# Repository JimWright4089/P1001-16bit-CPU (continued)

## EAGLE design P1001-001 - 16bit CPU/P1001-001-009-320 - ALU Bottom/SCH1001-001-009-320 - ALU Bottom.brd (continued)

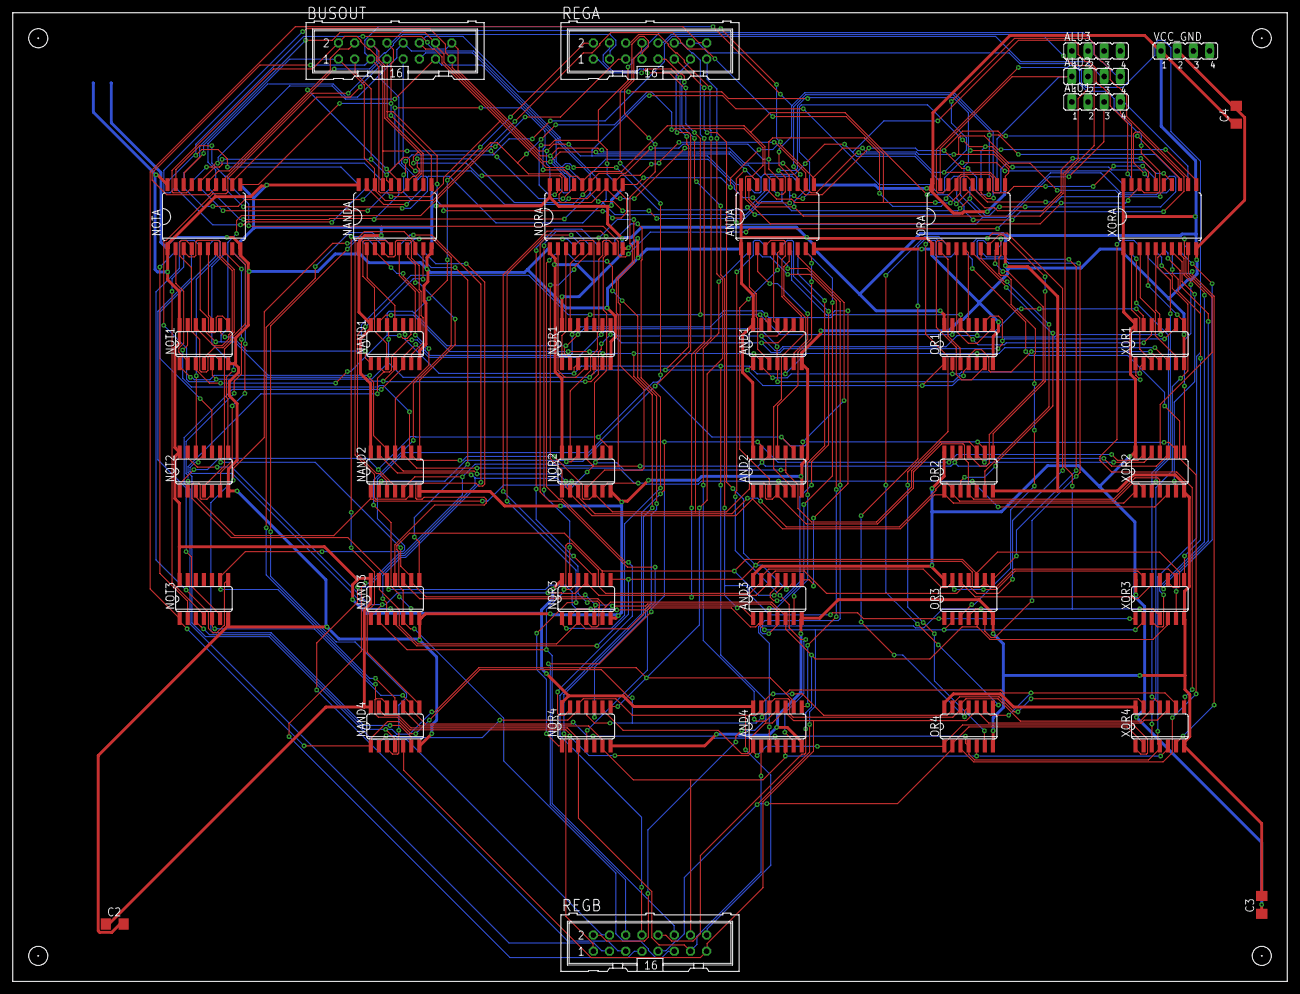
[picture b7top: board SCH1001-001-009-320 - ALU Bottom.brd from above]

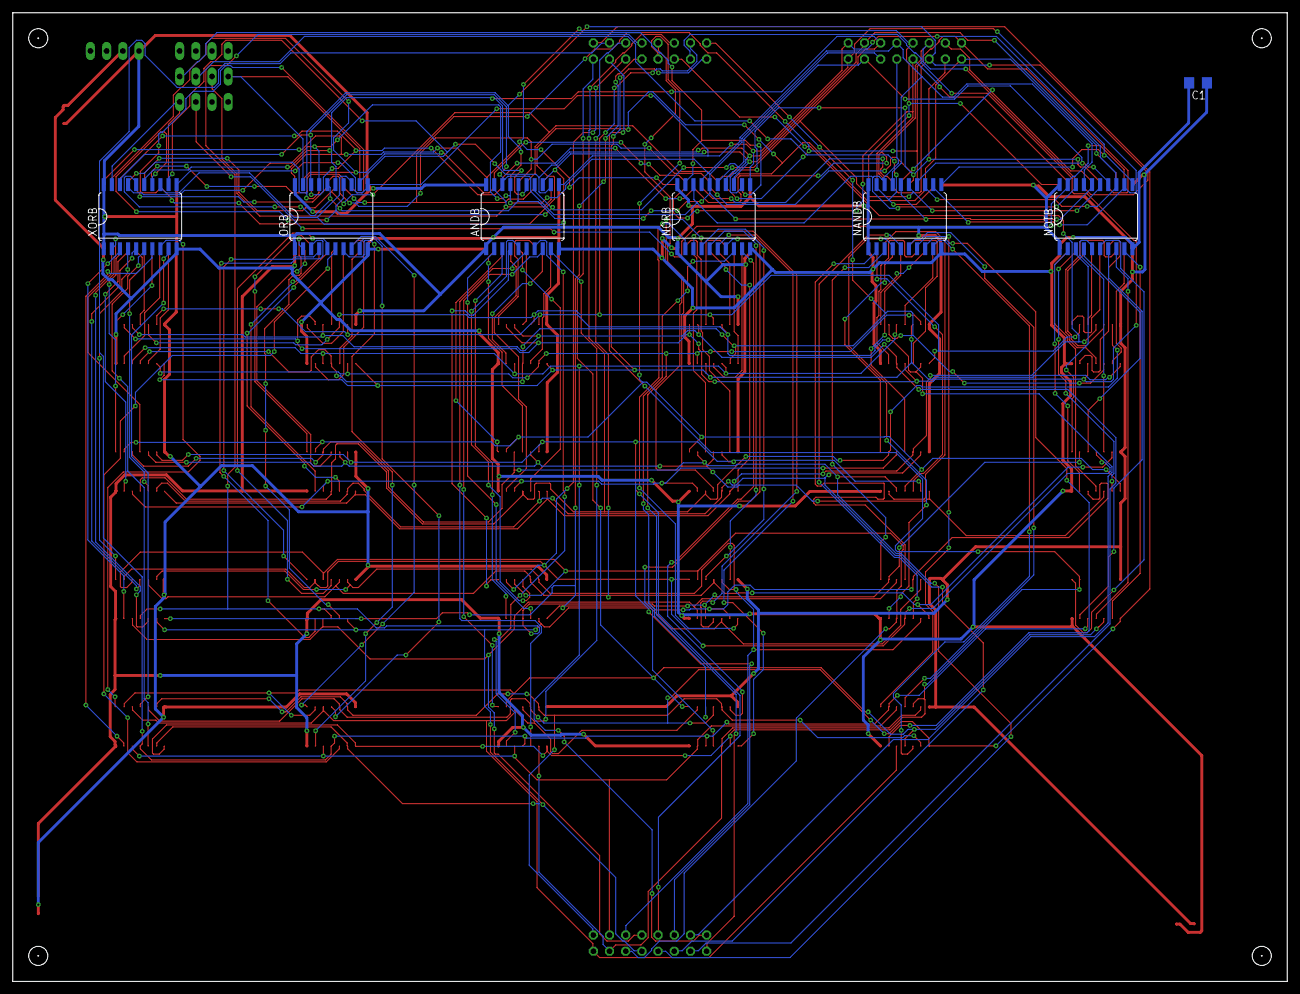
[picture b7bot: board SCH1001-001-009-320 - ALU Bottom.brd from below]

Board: 2 copper layers, 200.0 x 152.0 mm, 46 parts (7 on the bottom side), 152 nets.

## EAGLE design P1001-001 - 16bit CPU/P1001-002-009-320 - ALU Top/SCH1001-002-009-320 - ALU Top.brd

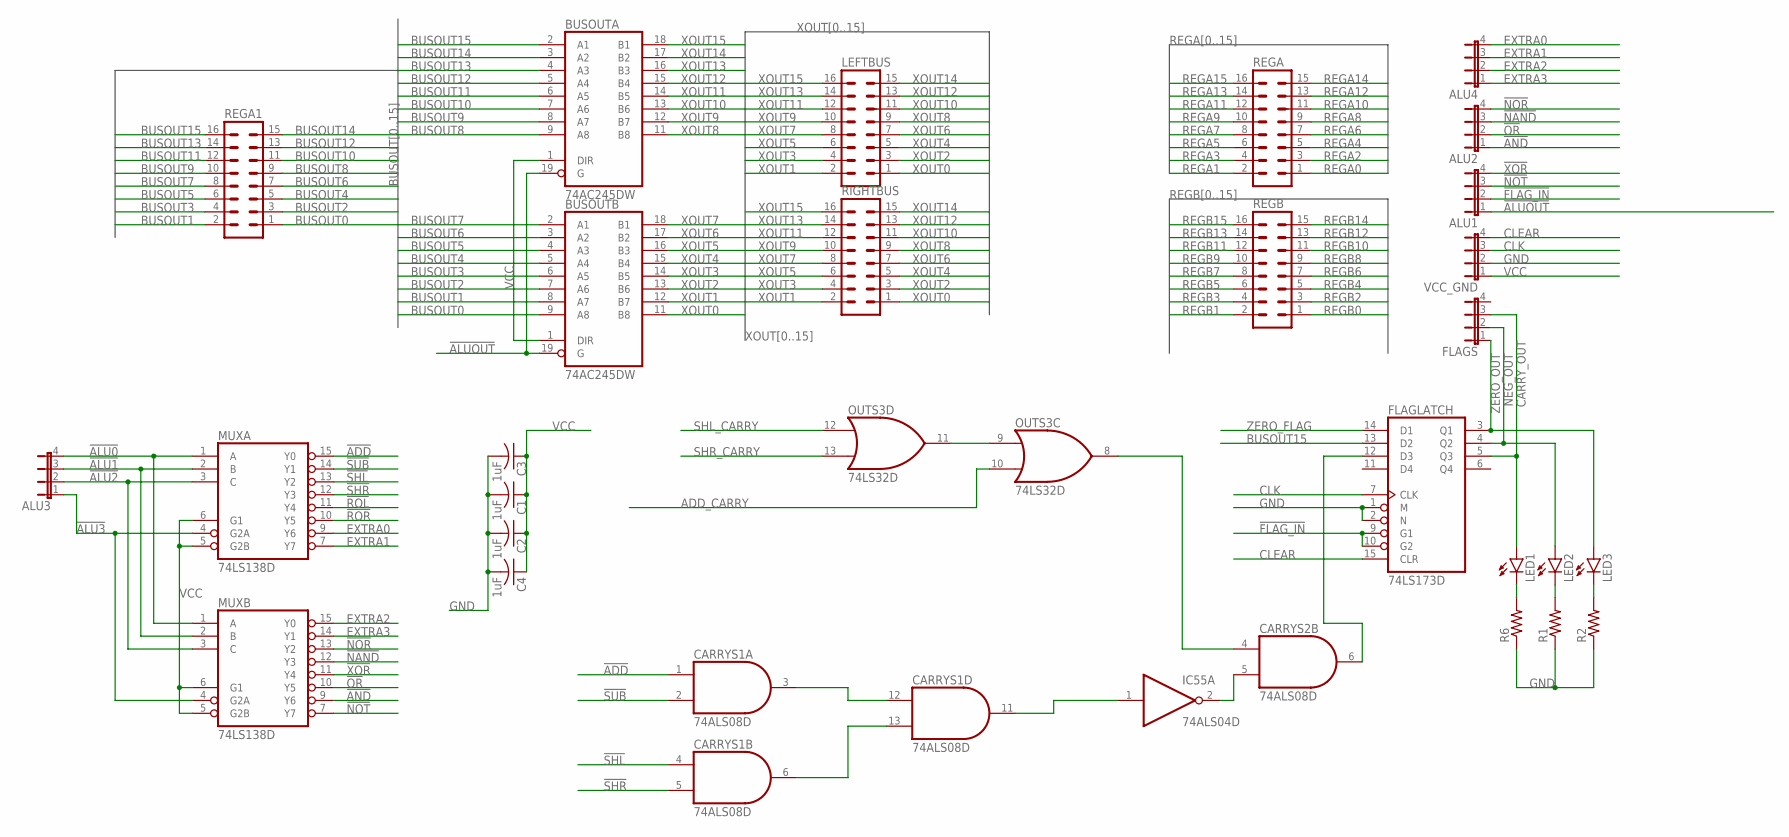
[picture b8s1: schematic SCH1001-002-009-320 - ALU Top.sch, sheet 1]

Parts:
ALU1, ALU2, ALU3, ALU4: JP4E; JP4
BUSOUTA: 74AC245DW; SO20W
BUSOUTB: 74AC245DW; SO20W
C1, C2, C3, C4: 1uF; C1206
CARRYS1, CARRYS2: 74ALS08D; SO14
FLAGLATCH: 74LS173D; SO16
FLAGS: JP4E; JP4
IC55: 74ALS04D; SO14
LED1, LED2, LED3: LED5MM
LEFTBUS: ML16
MUXA: 74LS138D; SO16
MUXB: 74LS138D; SO16
OUTS3: 74LS32D; SO14
R1, R2, R6: R-US_M1206; M1206
REGA, REGA1: ML16
REGB: ML16
RIGHTBUS: ML16
VCC_GND: JP4E; JP4

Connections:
!ADD: CARRYS1.1 (I0), MUXA.15 (Y0); also elsewhere on the board
!ALU0: ALU3.4, MUXA.1 (A), MUXB.1 (A)
!ALU1: ALU3.3, MUXA.2 (B), MUXB.2 (B)
!ALU2: ALU3.2, MUXA.3 (C), MUXB.3 (C)
!ALU3: ALU3.1, MUXA.4 (G2A), MUXB.4 (G2A)
!ALUOUT: ALU1.1, BUSOUTA.19 (G), BUSOUTB.19 (G)
!AND: ALU2.1, MUXB.9 (Y6)
!FLAG_IN: ALU1.2, FLAGLATCH.9 (G1), FLAGLATCH.10 (G2)
!NAND: ALU2.3, MUXB.12 (Y3)
!NOR: ALU2.4, MUXB.13 (Y2)
!NOT: ALU1.3, MUXB.7 (Y7)
!OR: ALU2.2, MUXB.10 (Y5)
!ROL: MUXA.11 (Y4); also elsewhere on the board
!ROR: MUXA.10 (Y5); also elsewhere on the board
!SHL: CARRYS1.4 (I0), MUXA.13 (Y2); also elsewhere on the board
!SHR: CARRYS1.5 (I1), MUXA.12 (Y3); also elsewhere on the board
!SUB: CARRYS1.2 (I1), MUXA.14 (Y1); also elsewhere on the board
!XOR: ALU1.4, MUXB.11 (Y4)
ADD_CARRY: OUTS3.10 (I1); also elsewhere on the board
BUSOUT0: BUSOUTB.9 (A8), REGA1.1; also elsewhere on the board
BUSOUT1: BUSOUTB.8 (A7), REGA1.2; also elsewhere on the board
BUSOUT2: BUSOUTB.7 (A6), REGA1.3; also elsewhere on the board
BUSOUT3: BUSOUTB.6 (A5), REGA1.4; also elsewhere on the board
BUSOUT4: BUSOUTB.5 (A4), REGA1.5; also elsewhere on the board
BUSOUT5: BUSOUTB.4 (A3), REGA1.6; also elsewhere on the board
BUSOUT6: BUSOUTB.3 (A2), REGA1.7; also elsewhere on the board
BUSOUT7: BUSOUTB.2 (A1), REGA1.8; also elsewhere on the board
BUSOUT8: BUSOUTA.9 (A8), REGA1.9; also elsewhere on the board
BUSOUT9: BUSOUTA.8 (A7), REGA1.10; also elsewhere on the board
BUSOUT10: BUSOUTA.7 (A6), REGA1.11; also elsewhere on the board
BUSOUT11: BUSOUTA.6 (A5), REGA1.12; also elsewhere on the board
BUSOUT12: BUSOUTA.5 (A4), REGA1.13; also elsewhere on the board
BUSOUT13: BUSOUTA.4 (A3), REGA1.14; also elsewhere on the board
BUSOUT14: BUSOUTA.3 (A2), REGA1.15; also elsewhere on the board
BUSOUT15: BUSOUTA.2 (A1), FLAGLATCH.13 (D2), REGA1.16; also elsewhere on the board
CARRY_OUT: FLAGLATCH.5 (Q3), FLAGS.3, LED1.A
CLEAR: FLAGLATCH.15 (CLR), VCC_GND.4
CLK: FLAGLATCH.7 (CLK), VCC_GND.3
EXTRA0: ALU4.4, MUXA.9 (Y6)
EXTRA1: ALU4.3, MUXA.7 (Y7)
EXTRA2: ALU4.2, MUXB.15 (Y0)
EXTRA3: ALU4.1, MUXB.14 (Y1)
GND: BUSOUTA.10 (GND), BUSOUTB.10 (GND), C1.2, C2.2, C3.2, C4.2, CARRYS1.7 (GND), CARRYS2.7 (GND), FLAGLATCH.1 (M), FLAGLATCH.2 (N), FLAGLATCH.8 (GND), IC55.7 (GND), MUXA.8 (GND), MUXB.8 (GND), OUTS3.7 (GND), R1.1, R2.1, R6.1, VCC_GND.2; also elsewhere on the board
unnamed: OUTS3.9 (I0), OUTS3.11 (O)
unnamed: CARRYS2.4 (I0), OUTS3.8 (O)
unnamed: CARRYS2.6 (O), FLAGLATCH.12 (D3)
unnamed: CARRYS2.5 (I1), IC55.2 (O)
unnamed: CARRYS1.11 (O), IC55.1 (I)
unnamed: CARRYS1.3 (O), CARRYS1.12 (I0)
unnamed: CARRYS1.6 (O), CARRYS1.13 (I1)
unnamed: LED1.K (C), R6.2
unnamed: LED2.K (C), R1.2
unnamed: LED3.K (C), R2.2
NEG_OUT: FLAGLATCH.4 (Q2), FLAGS.2, LED2.A
REGA0: REGA.1; also elsewhere on the board
REGA1: REGA.2; also elsewhere on the board
REGA2: REGA.3; also elsewhere on the board
REGA3: REGA.4; also elsewhere on the board
REGA4: REGA.5; also elsewhere on the board
REGA5: REGA.6; also elsewhere on the board
REGA6: REGA.7; also elsewhere on the board
REGA7: REGA.8; also elsewhere on the board
REGA8: REGA.9; also elsewhere on the board
REGA9: REGA.10; also elsewhere on the board
REGA10: REGA.11; also elsewhere on the board
REGA11: REGA.12; also elsewhere on the board
REGA12: REGA.13; also elsewhere on the board
REGA13: REGA.14; also elsewhere on the board
REGA14: REGA.15; also elsewhere on the board
REGA15: REGA.16; also elsewhere on the board
REGB0: REGB.1; also elsewhere on the board
REGB1: REGB.2; also elsewhere on the board
REGB2: REGB.3; also elsewhere on the board
REGB3: REGB.4; also elsewhere on the board
REGB4: REGB.5; also elsewhere on the board
REGB5: REGB.6; also elsewhere on the board
REGB6: REGB.7; also elsewhere on the board
REGB7: REGB.8; also elsewhere on the board
REGB8: REGB.9; also elsewhere on the board
REGB9: REGB.10; also elsewhere on the board
REGB10: REGB.11; also elsewhere on the board
REGB11: REGB.12; also elsewhere on the board
REGB12: REGB.13; also elsewhere on the board
REGB13: REGB.14; also elsewhere on the board
REGB14: REGB.15; also elsewhere on the board
REGB15: REGB.16; also elsewhere on the board
SHL_CARRY: OUTS3.12 (I0); also elsewhere on the board
SHR_CARRY: OUTS3.13 (I1); also elsewhere on the board
VCC: BUSOUTA.1 (DIR), BUSOUTA.20 (VCC), BUSOUTB.1 (DIR), BUSOUTB.20 (VCC), C1.1, C2.1, C3.1, C4.1, CARRYS1.14 (VCC), CARRYS2.14 (VCC), FLAGLATCH.16 (VCC), IC55.14 (VCC), MUXA.5 (G2B), MUXA.6 (G1), MUXA.16 (VCC), MUXB.5 (G2B), MUXB.6 (G1), MUXB.16 (VCC), OUTS3.14 (VCC), VCC_GND.1; also elsewhere on the board
XOUT0: BUSOUTB.11 (B8), LEFTBUS.1, RIGHTBUS.1
XOUT1: BUSOUTB.12 (B7), LEFTBUS.2, RIGHTBUS.2
XOUT2: BUSOUTB.13 (B6), LEFTBUS.3, RIGHTBUS.3
XOUT3: BUSOUTB.14 (B5), LEFTBUS.4, RIGHTBUS.4
XOUT4: BUSOUTB.15 (B4), LEFTBUS.5, RIGHTBUS.5
XOUT5: BUSOUTB.16 (B3), LEFTBUS.6, RIGHTBUS.6
XOUT6: BUSOUTB.17 (B2), LEFTBUS.7, RIGHTBUS.7
XOUT7: BUSOUTB.18 (B1), LEFTBUS.8, RIGHTBUS.8
XOUT8: BUSOUTA.11 (B8), LEFTBUS.9, RIGHTBUS.9
XOUT9: BUSOUTA.12 (B7), LEFTBUS.10, RIGHTBUS.10
XOUT10: BUSOUTA.13 (B6), LEFTBUS.11, RIGHTBUS.11
XOUT11: BUSOUTA.14 (B5), LEFTBUS.12, RIGHTBUS.12
XOUT12: BUSOUTA.15 (B4), LEFTBUS.13, RIGHTBUS.13
XOUT13: BUSOUTA.16 (B3), LEFTBUS.14, RIGHTBUS.14
XOUT14: BUSOUTA.17 (B2), LEFTBUS.15, RIGHTBUS.15
XOUT15: BUSOUTA.18 (B1), LEFTBUS.16, RIGHTBUS.16
ZERO_FLAG: FLAGLATCH.14 (D1); also elsewhere on the board
ZERO_OUT: FLAGLATCH.3 (Q1), FLAGS.1, LED3.A

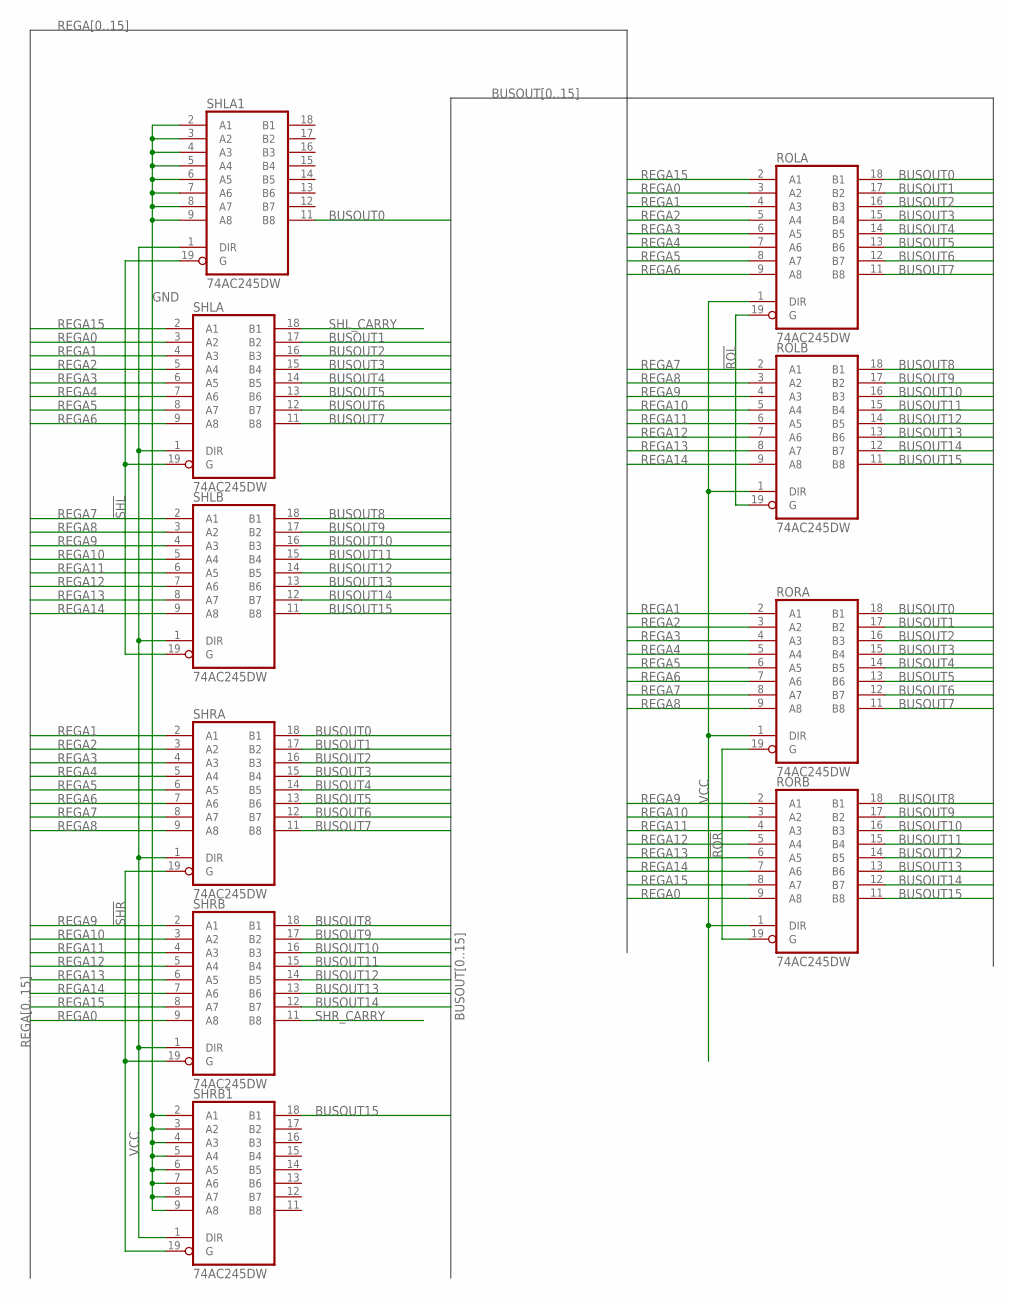
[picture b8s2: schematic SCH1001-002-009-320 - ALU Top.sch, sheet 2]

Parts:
ROLA: 74AC245DW; SO20W
ROLB: 74AC245DW; SO20W
RORA: 74AC245DW; SO20W
RORB: 74AC245DW; SO20W
SHLA, SHLA1: 74AC245DW; SO20W
SHLB: 74AC245DW; SO20W
SHRA: 74AC245DW; SO20W
SHRB, SHRB1: 74AC245DW; SO20W

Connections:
!ROL: ROLA.19 (G), ROLB.19 (G); also elsewhere on the board
!ROR: RORA.19 (G), RORB.19 (G); also elsewhere on the board
!SHL: SHLA.19 (G), SHLA1.19 (G), SHLB.19 (G); also elsewhere on the board
!SHR: SHRA.19 (G), SHRB.19 (G), SHRB1.19 (G); also elsewhere on the board
BUSOUT0: ROLA.18 (B1), RORA.18 (B1), SHLA1.11 (B8), SHRA.18 (B1); also elsewhere on the board
BUSOUT1: ROLA.17 (B2), RORA.17 (B2), SHLA.17 (B2), SHRA.17 (B2); also elsewhere on the board
BUSOUT2: ROLA.16 (B3), RORA.16 (B3), SHLA.16 (B3), SHRA.16 (B3); also elsewhere on the board
BUSOUT3: ROLA.15 (B4), RORA.15 (B4), SHLA.15 (B4), SHRA.15 (B4); also elsewhere on the board
BUSOUT4: ROLA.14 (B5), RORA.14 (B5), SHLA.14 (B5), SHRA.14 (B5); also elsewhere on the board
BUSOUT5: ROLA.13 (B6), RORA.13 (B6), SHLA.13 (B6), SHRA.13 (B6); also elsewhere on the board
BUSOUT6: ROLA.12 (B7), RORA.12 (B7), SHLA.12 (B7), SHRA.12 (B7); also elsewhere on the board
BUSOUT7: ROLA.11 (B8), RORA.11 (B8), SHLA.11 (B8), SHRA.11 (B8); also elsewhere on the board
BUSOUT8: ROLB.18 (B1), RORB.18 (B1), SHLB.18 (B1), SHRB.18 (B1); also elsewhere on the board
BUSOUT9: ROLB.17 (B2), RORB.17 (B2), SHLB.17 (B2), SHRB.17 (B2); also elsewhere on the board
BUSOUT10: ROLB.16 (B3), RORB.16 (B3), SHLB.16 (B3), SHRB.16 (B3); also elsewhere on the board
BUSOUT11: ROLB.15 (B4), RORB.15 (B4), SHLB.15 (B4), SHRB.15 (B4); also elsewhere on the board
BUSOUT12: ROLB.14 (B5), RORB.14 (B5), SHLB.14 (B5), SHRB.14 (B5); also elsewhere on the board
BUSOUT13: ROLB.13 (B6), RORB.13 (B6), SHLB.13 (B6), SHRB.13 (B6); also elsewhere on the board
BUSOUT14: ROLB.12 (B7), RORB.12 (B7), SHLB.12 (B7), SHRB.12 (B7); also elsewhere on the board
BUSOUT15: ROLB.11 (B8), RORB.11 (B8), SHLB.11 (B8), SHRB1.18 (B1); also elsewhere on the board
GND: ROLA.10 (GND), ROLB.10 (GND), RORA.10 (GND), RORB.10 (GND), SHLA.10 (GND), SHLA1.2 (A1), SHLA1.3 (A2), SHLA1.4 (A3), SHLA1.5 (A4), SHLA1.6 (A5), SHLA1.7 (A6), SHLA1.8 (A7), SHLA1.9 (A8), SHLA1.10 (GND), SHLB.10 (GND), SHRA.10 (GND), SHRB.10 (GND), SHRB1.2 (A1), SHRB1.3 (A2), SHRB1.4 (A3), SHRB1.5 (A4), SHRB1.6 (A5), SHRB1.7 (A6), SHRB1.8 (A7), SHRB1.9 (A8), SHRB1.10 (GND); also elsewhere on the board
REGA0: ROLA.3 (A2), RORB.9 (A8), SHLA.3 (A2), SHRB.9 (A8); also elsewhere on the board
REGA1: ROLA.4 (A3), RORA.2 (A1), SHLA.4 (A3), SHRA.2 (A1); also elsewhere on the board
REGA2: ROLA.5 (A4), RORA.3 (A2), SHLA.5 (A4), SHRA.3 (A2); also elsewhere on the board
REGA3: ROLA.6 (A5), RORA.4 (A3), SHLA.6 (A5), SHRA.4 (A3); also elsewhere on the board
REGA4: ROLA.7 (A6), RORA.5 (A4), SHLA.7 (A6), SHRA.5 (A4); also elsewhere on the board
REGA5: ROLA.8 (A7), RORA.6 (A5), SHLA.8 (A7), SHRA.6 (A5); also elsewhere on the board
REGA6: ROLA.9 (A8), RORA.7 (A6), SHLA.9 (A8), SHRA.7 (A6); also elsewhere on the board
REGA7: ROLB.2 (A1), RORA.8 (A7), SHLB.2 (A1), SHRA.8 (A7); also elsewhere on the board
REGA8: ROLB.3 (A2), RORA.9 (A8), SHLB.3 (A2), SHRA.9 (A8); also elsewhere on the board
REGA9: ROLB.4 (A3), RORB.2 (A1), SHLB.4 (A3), SHRB.2 (A1); also elsewhere on the board
REGA10: ROLB.5 (A4), RORB.3 (A2), SHLB.5 (A4), SHRB.3 (A2); also elsewhere on the board
REGA11: ROLB.6 (A5), RORB.4 (A3), SHLB.6 (A5), SHRB.4 (A3); also elsewhere on the board
REGA12: ROLB.7 (A6), RORB.5 (A4), SHLB.7 (A6), SHRB.5 (A4); also elsewhere on the board
REGA13: ROLB.8 (A7), RORB.6 (A5), SHLB.8 (A7), SHRB.6 (A5); also elsewhere on the board
REGA14: ROLB.9 (A8), RORB.7 (A6), SHLB.9 (A8), SHRB.7 (A6); also elsewhere on the board
REGA15: ROLA.2 (A1), RORB.8 (A7), SHLA.2 (A1), SHRB.8 (A7); also elsewhere on the board
SHL_CARRY: SHLA.18 (B1); also elsewhere on the board
SHR_CARRY: SHRB.11 (B8); also elsewhere on the board
VCC: ROLA.1 (DIR), ROLA.20 (VCC), ROLB.1 (DIR), ROLB.20 (VCC), RORA.1 (DIR), RORA.20 (VCC), RORB.1 (DIR), RORB.20 (VCC), SHLA.1 (DIR), SHLA.20 (VCC), SHLA1.1 (DIR), SHLA1.20 (VCC), SHLB.1 (DIR), SHLB.20 (VCC), SHRA.1 (DIR), SHRA.20 (VCC), SHRB.1 (DIR), SHRB.20 (VCC), SHRB1.1 (DIR), SHRB1.20 (VCC); also elsewhere on the board

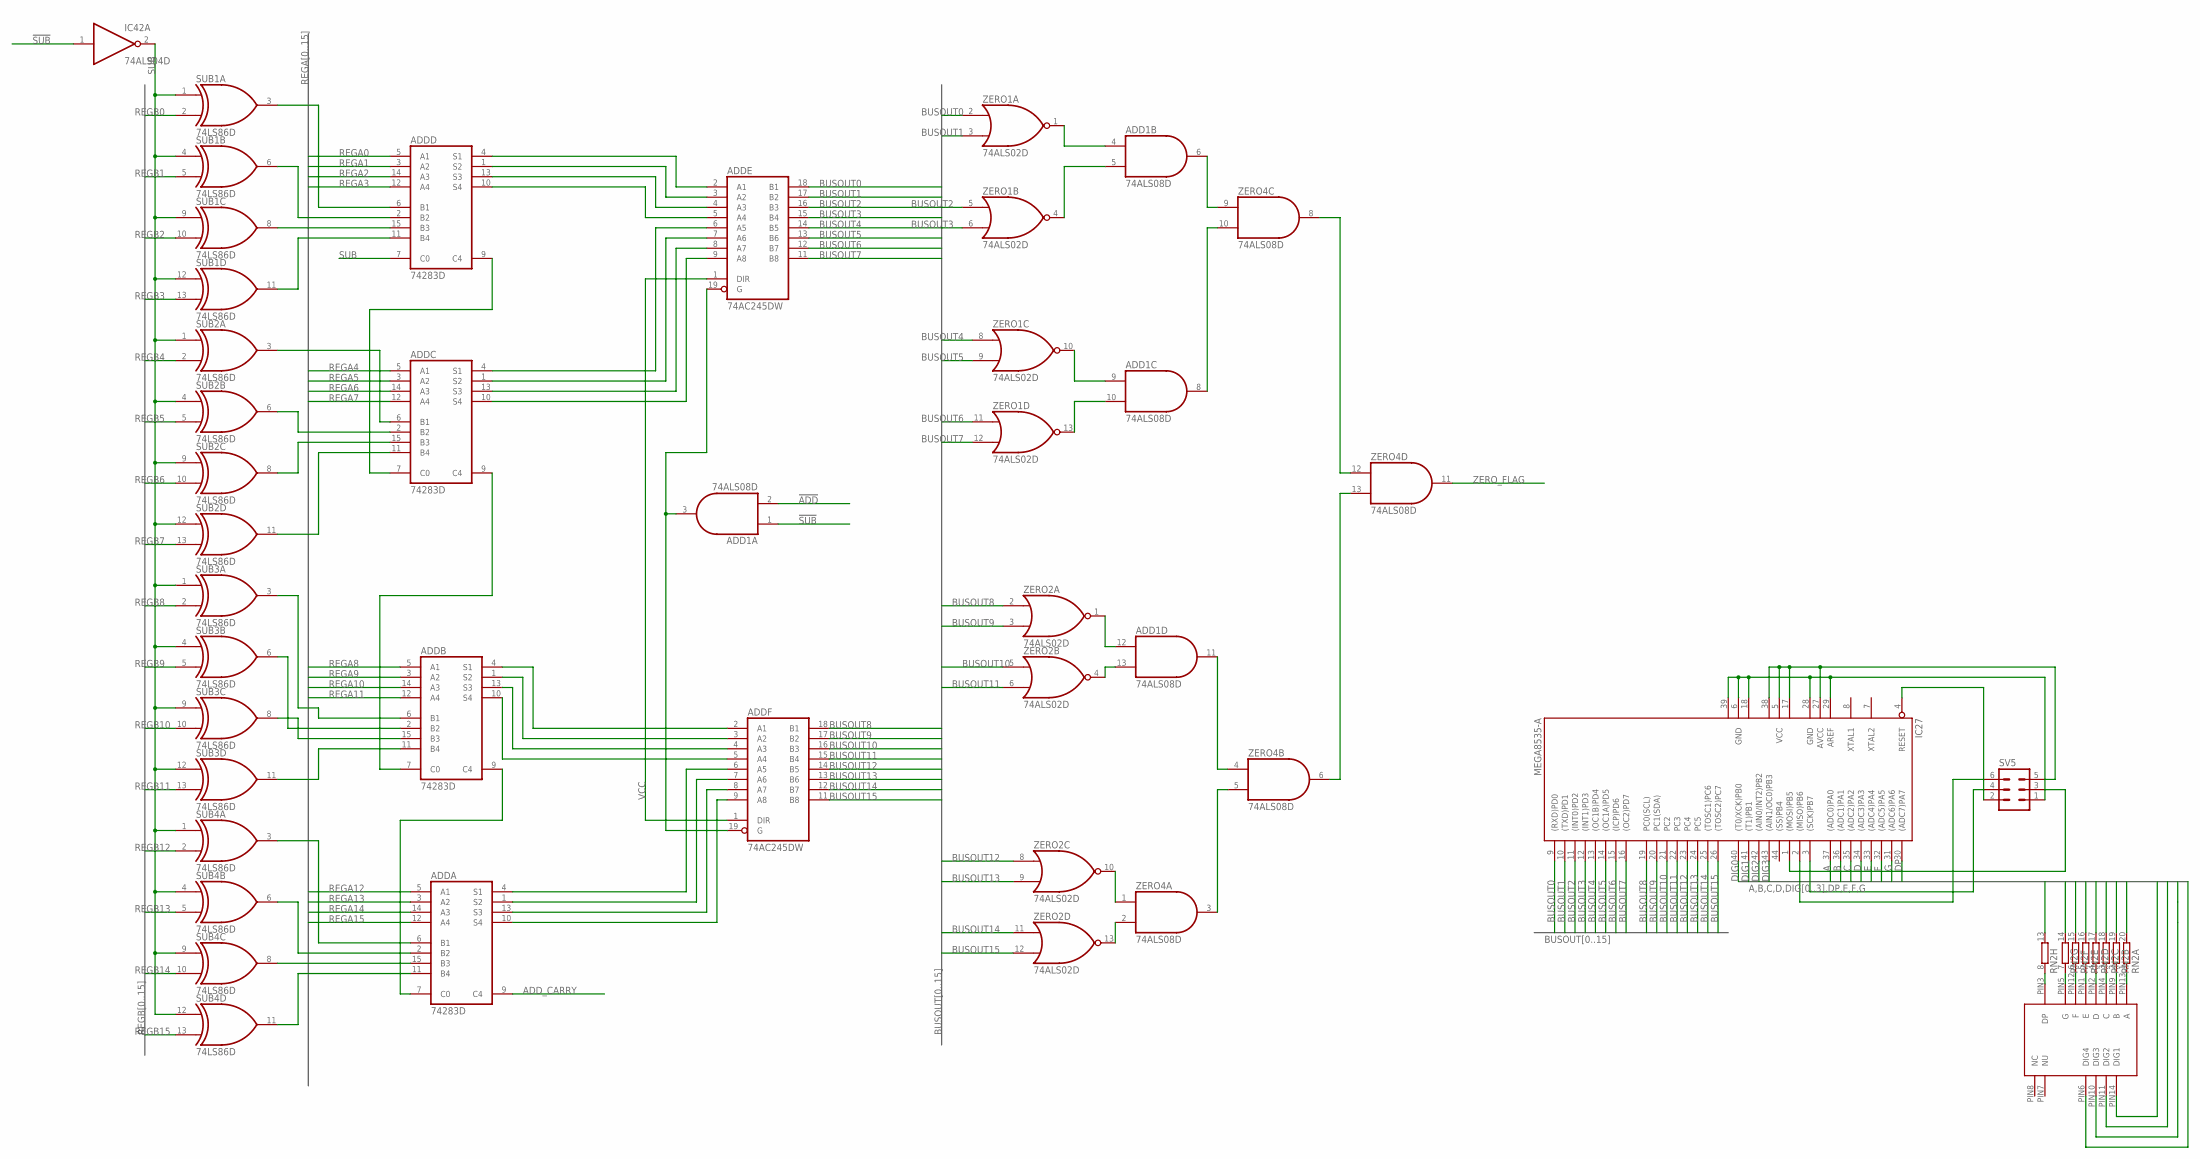
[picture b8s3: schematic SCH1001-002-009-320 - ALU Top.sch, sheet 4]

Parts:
ADD1: 74ALS08D; SO14
ADDA: 74283D; SO16
ADDB: 74283D; SO16
ADDC: 74283D; SO16
ADDD: 74283D; SO16
ADDE: 74AC245DW; SO20W
ADDF: 74AC245DW; SO20W
IC27: MEGA8535-A; TQFP44
IC42: 74ALS04D; SO14
RN2: 10R-NSOMC; SOMC20
SUB1, SUB2, SUB3, SUB4: 74LS86D; SO14
SV5: ML6
U$1: 4-DIGIT-7-SEGMENT
ZERO1, ZERO2: 74ALS02D; SO14
ZERO4: 74ALS08D; SO14

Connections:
!ADD: ADD1.2 (I1); also elsewhere on the board
!SUB: ADD1.1 (I0), IC42.1 (I); also elsewhere on the board
A: IC27.37 ((ADC0)PA0), RN2.20 (2)
ADD_CARRY: ADDA.9 (C4); also elsewhere on the board
B: IC27.36 ((ADC1)PA1), RN2.19 (2)
BUSOUT0: ADDE.18 (B1), IC27.9 ((RXD)PD0), ZERO1.2 (I0); also elsewhere on the board
BUSOUT1: ADDE.17 (B2), IC27.10 ((TXD)PD1), ZERO1.3 (I1); also elsewhere on the board
BUSOUT2: ADDE.16 (B3), IC27.11 ((INT0)PD2), ZERO1.5 (I0); also elsewhere on the board
BUSOUT3: ADDE.15 (B4), IC27.12 ((INT1)PD3), ZERO1.6 (I1); also elsewhere on the board
BUSOUT4: ADDE.14 (B5), IC27.13 ((OC1B)PD4), ZERO1.8 (I0); also elsewhere on the board
BUSOUT5: ADDE.13 (B6), IC27.14 ((OC1A)PD5), ZERO1.9 (I1); also elsewhere on the board
BUSOUT6: ADDE.12 (B7), IC27.15 ((ICP)PD6), ZERO1.11 (I0); also elsewhere on the board
BUSOUT7: ADDE.11 (B8), IC27.16 ((OC2)PD7), ZERO1.12 (I1); also elsewhere on the board
BUSOUT8: ADDF.18 (B1), IC27.19 (PC0(SCL)), ZERO2.2 (I0); also elsewhere on the board
BUSOUT9: ADDF.17 (B2), IC27.20 (PC1(SDA)), ZERO2.3 (I1); also elsewhere on the board
BUSOUT10: ADDF.16 (B3), IC27.21 (PC2), ZERO2.5 (I0); also elsewhere on the board
BUSOUT11: ADDF.15 (B4), IC27.22 (PC3), ZERO2.6 (I1); also elsewhere on the board
BUSOUT12: ADDF.14 (B5), IC27.23 (PC4), ZERO2.8 (I0); also elsewhere on the board
BUSOUT13: ADDF.13 (B6), IC27.24 (PC5), ZERO2.9 (I1); also elsewhere on the board
BUSOUT14: ADDF.12 (B7), IC27.25 ((TOSC1)PC6), ZERO2.11 (I0); also elsewhere on the board
BUSOUT15: ADDF.11 (B8), IC27.26 ((TOSC2)PC7), ZERO2.12 (I1); also elsewhere on the board
C: IC27.35 ((ADC2)PA2), RN2.18 (2)
D: IC27.34 ((ADC3)PA3), RN2.17 (2)
DIG0: IC27.40 ((T0/XCK)PB0), U$1.PIN14 (DIG1)
DIG1: IC27.41 ((T1)PB1), U$1.PIN11 (DIG2)
DIG2: IC27.42 ((AIN0/INT2)PB2), U$1.PIN10 (DIG3)
DIG3: IC27.43 ((AIN1/OC0)PB3), U$1.PIN6 (DIG4)
DP: IC27.30 ((ADC7)PA7), RN2.13 (2)
E: IC27.33 ((ADC4)PA4), RN2.16 (2)
F: IC27.32 ((ADC5)PA5), RN2.15 (2)
G: IC27.31 ((ADC6)PA6), RN2.14 (2)
GND: ADD1.7 (GND), ADDA.8 (GND), ADDB.8 (GND), ADDC.8 (GND), ADDD.8 (GND), ADDE.10 (GND), ADDF.10 (GND), IC42.7 (GND), SUB1.7 (GND), SUB2.7 (GND), SUB3.7 (GND), SUB4.7 (GND), ZERO1.7 (GND), ZERO2.7 (GND), ZERO4.7 (GND); also elsewhere on the board
unnamed: ADDD.6 (B1), SUB1.3 (O)
unnamed: ADDD.2 (B2), SUB1.6 (O)
unnamed: ADDD.15 (B3), SUB1.8 (O)
unnamed: ADDD.11 (B4), SUB1.11 (O)
unnamed: ADDD.4 (S1), ADDE.2 (A1)
unnamed: ADDD.1 (S2), ADDE.3 (A2)
unnamed: ADDC.10 (S4), ADDE.9 (A8)
unnamed: ADDC.13 (S3), ADDE.8 (A7)
unnamed: ADDC.1 (S2), ADDE.7 (A6)
unnamed: ADDC.4 (S1), ADDE.6 (A5)
unnamed: ADDC.6 (B1), SUB2.3 (O)
unnamed: ADDC.2 (B2), SUB2.6 (O)
unnamed: ADDC.15 (B3), SUB2.8 (O)
unnamed: ADDC.11 (B4), SUB2.11 (O)
unnamed: ADDC.7 (C0), ADDD.9 (C4)
unnamed: ADDA.2 (B2), SUB4.6 (O)
unnamed: ADDA.15 (B3), SUB4.8 (O)
unnamed: ADDA.11 (B4), SUB4.11 (O)
unnamed: ADDA.6 (B1), SUB4.3 (O)
unnamed: ADDA.7 (C0), ADDB.9 (C4)
unnamed: ADDA.10 (S4), ADDF.9 (A8)
unnamed: ADDA.13 (S3), ADDF.8 (A7)
unnamed: ADDA.1 (S2), ADDF.7 (A6)
unnamed: ADDA.4 (S1), ADDF.6 (A5)
unnamed: ADDB.11 (B4), SUB3.11 (O)
unnamed: ADDB.15 (B3), SUB3.8 (O)
unnamed: ADDB.2 (B2), SUB3.6 (O)
unnamed: ADDB.6 (B1), SUB3.3 (O)
unnamed: ADDB.7 (C0), ADDC.9 (C4)
unnamed: ADDB.10 (S4), ADDF.5 (A4)
unnamed: ADDB.13 (S3), ADDF.4 (A3)
unnamed: ADDB.1 (S2), ADDF.3 (A2)
unnamed: ADDB.4 (S1), ADDF.2 (A1)
unnamed: ADD1.3 (O), ADDE.19 (G), ADDF.19 (G)
unnamed: ADD1.4 (I0), ZERO1.1 (O)
unnamed: ADD1.5 (I1), ZERO1.4 (O)
unnamed: ADD1.9 (I0), ZERO1.10 (O)
unnamed: ADD1.10 (I1), ZERO1.13 (O)
unnamed: ADD1.8 (O), ZERO4.10 (I1)
unnamed: ADD1.6 (O), ZERO4.9 (I0)
unnamed: ZERO4.8 (O), ZERO4.12 (I0)
unnamed: ZERO4.6 (O), ZERO4.13 (I1)
unnamed: ADD1.11 (O), ZERO4.4 (I0)
unnamed: ZERO4.3 (O), ZERO4.5 (I1)
unnamed: ZERO2.10 (O), ZERO4.1 (I0)
unnamed: ZERO2.13 (O), ZERO4.2 (I1)
unnamed: ADD1.12 (I0), ZERO2.1 (O)
unnamed: ADD1.13 (I1), ZERO2.4 (O)
unnamed: ADDD.13 (S3), ADDE.4 (A3)
unnamed: ADDD.10 (S4), ADDE.5 (A4)
unnamed: IC27.1 ((MOSI)PB5), SV5.3
unnamed: IC27.3 ((SCK)PB7), SV5.4
unnamed: IC27.2 ((MISO)PB6), SV5.6
unnamed: IC27.4 (RESET), SV5.2
unnamed: RN2.1, U$1.PIN13 (A)
unnamed: RN2.2 (1), U$1.PIN9 (B)
unnamed: RN2.3 (1), U$1.PIN4 (C)
unnamed: RN2.4 (1), U$1.PIN2 (D)
unnamed: RN2.5 (1), U$1.PIN1 (E)
unnamed: RN2.6 (1), U$1.PIN12 (F)
unnamed: RN2.7 (1), U$1.PIN5 (G)
unnamed: RN2.8 (1), U$1.PIN3 (DP)
unnamed: IC27.5 (VCC), IC27.17 (VCC1), IC27.27 (AVCC), IC27.38 (VCC2), SV5.5
unnamed: IC27.6 (GND), IC27.18 (GND1), IC27.28 (GND), IC27.29 (AREF), IC27.39 (GND2), SV5.1
REGA0: ADDD.5 (A1); also elsewhere on the board
REGA1: ADDD.3 (A2); also elsewhere on the board
REGA2: ADDD.14 (A3); also elsewhere on the board
REGA3: ADDD.12 (A4); also elsewhere on the board
REGA4: ADDC.5 (A1); also elsewhere on the board
REGA5: ADDC.3 (A2); also elsewhere on the board
REGA6: ADDC.14 (A3); also elsewhere on the board
REGA7: ADDC.12 (A4); also elsewhere on the board
REGA8: ADDB.5 (A1); also elsewhere on the board
REGA9: ADDB.3 (A2); also elsewhere on the board
REGA10: ADDB.14 (A3); also elsewhere on the board
REGA11: ADDB.12 (A4); also elsewhere on the board
REGA12: ADDA.5 (A1); also elsewhere on the board
REGA13: ADDA.3 (A2); also elsewhere on the board
REGA14: ADDA.14 (A3); also elsewhere on the board
REGA15: ADDA.12 (A4); also elsewhere on the board
REGB0: SUB1.2 (I1); also elsewhere on the board
REGB1: SUB1.5 (I1); also elsewhere on the board
REGB2: SUB1.10 (I1); also elsewhere on the board
REGB3: SUB1.13 (I1); also elsewhere on the board
REGB4: SUB2.2 (I1); also elsewhere on the board
REGB5: SUB2.5 (I1); also elsewhere on the board
REGB6: SUB2.10 (I1); also elsewhere on the board
REGB7: SUB2.13 (I1); also elsewhere on the board
REGB8: SUB3.2 (I1); also elsewhere on the board
REGB9: SUB3.5 (I1); also elsewhere on the board
REGB10: SUB3.10 (I1); also elsewhere on the board
REGB11: SUB3.13 (I1); also elsewhere on the board
REGB12: SUB4.2 (I1); also elsewhere on the board
REGB13: SUB4.5 (I1); also elsewhere on the board
REGB14: SUB4.10 (I1); also elsewhere on the board
REGB15: SUB4.13 (I1); also elsewhere on the board
SUB: ADDD.7 (C0), IC42.2 (O), SUB1.1 (I0), SUB1.4 (I0), SUB1.9 (I0), SUB1.12 (I0), SUB2.1 (I0), SUB2.4 (I0), SUB2.9 (I0), SUB2.12 (I0), SUB3.1 (I0), SUB3.4 (I0), SUB3.9 (I0), SUB3.12 (I0), SUB4.1 (I0), SUB4.4 (I0), SUB4.9 (I0), SUB4.12 (I0)
VCC: ADD1.14 (VCC), ADDA.16 (VCC), ADDB.16 (VCC), ADDC.16 (VCC), ADDD.16 (VCC), ADDE.1 (DIR), ADDE.20 (VCC), ADDF.1 (DIR), ADDF.20 (VCC), IC42.14 (VCC), SUB1.14 (VCC), SUB2.14 (VCC), SUB3.14 (VCC), SUB4.14 (VCC), ZERO1.14 (VCC), ZERO2.14 (VCC), ZERO4.14 (VCC); also elsewhere on the board
ZERO_FLAG: ZERO4.11 (O); also elsewhere on the board

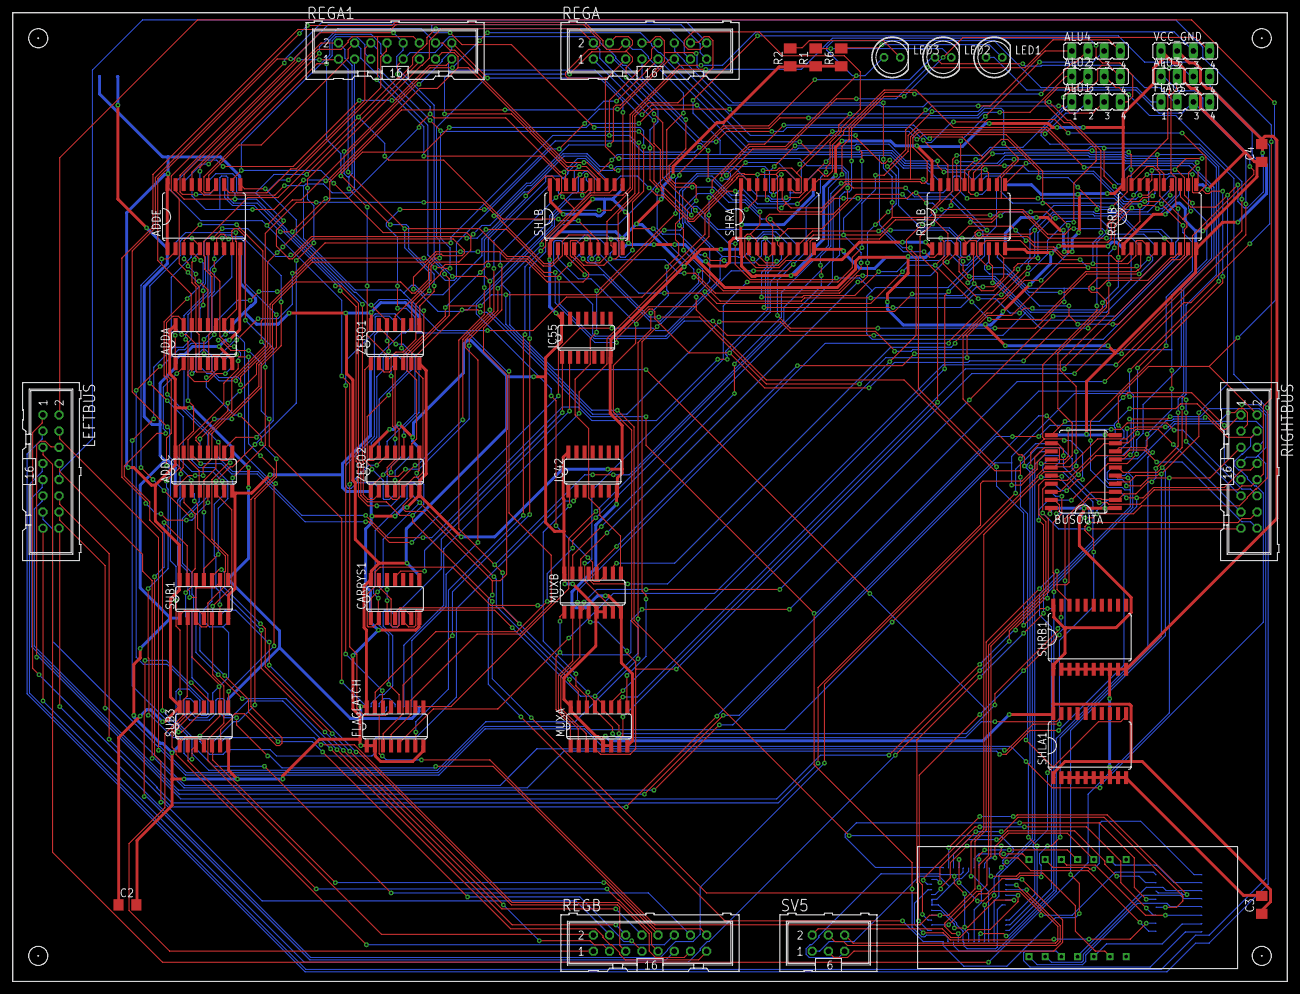
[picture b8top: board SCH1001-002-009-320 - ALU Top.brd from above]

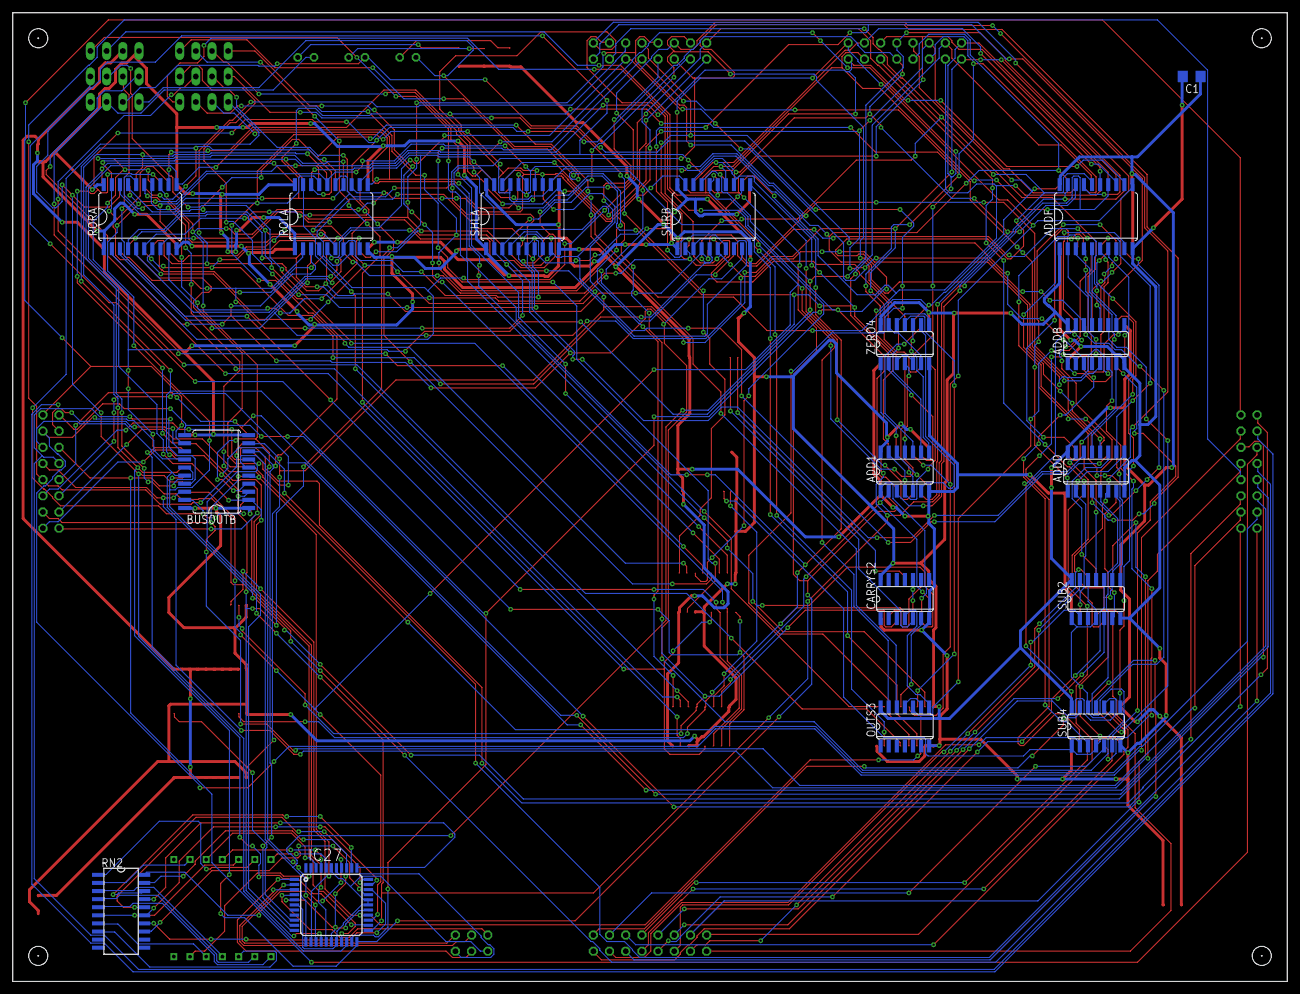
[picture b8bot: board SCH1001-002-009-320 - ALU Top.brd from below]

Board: 2 copper layers, 200.0 x 152.0 mm, 59 parts (17 on the bottom side), 184 nets.

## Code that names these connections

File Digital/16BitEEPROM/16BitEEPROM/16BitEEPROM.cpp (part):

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#define RAMout      | 0b100000000000000000000000000000000000000000000000
#define InterRegout | 0b100010000000000000000000000000000000000000000000
#define InterFlgout | 0b100100000000000000000000000000000000000000000000
#define ALUout      | 0b100110000000000000000000000000000000000000000000
#define Eout        | 0b101000000000000000000000000000000000000000000000
#define Fout        | 0b101010000000000000000000000000000000000000000000
#define Gout        | 0b101100000000000000000000000000000000000000000000
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#define Extra2out   | 0b110010000000000000000000000000000000000000000000
#define Extra3out   | 0b110100000000000000000000000000000000000000000000
#define Extra4out   | 0b110110000000000000000000000000000000000000000000
#define Extra1      & 0b111110111111111111111111111111111111111111111111
#define Extra2      & 0b111111011111111111111111111111111111111111111111
#define Extra3      & 0b111111101111111111111111111111111111111111111111
#define Extra4      | 0b000000001000000000000000000000000000000000000000
#define Areset      | 0b000000000100000000000000000000000000000000000000
#define Breset      | 0b000000000010000000000000000000000000000000000000
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#define RAMinH      & 0b111111111111111111111111111111101111111111111111

//                    0b000001110000000000000011111111110000111111100000
#define ADD         | 0b000000000000000000000000000000000000000000000000
#define SUB         | 0b000000000000000000000000000000000001000000000000
#define SHL         | 0b000000000000000000000000000000000010000000000000
#define SHR         | 0b000000000000000000000000000000000011000000000000
#define RLL         | 0b000000000000000000000000000000000100000000000000
#define RLR         | 0b000000000000000000000000000000000101000000000000
#define NOR         | 0b000000000000000000000000000000001010000000000000
#define NAND        | 0b000000000000000000000000000000001011000000000000
#define NOT         | 0b000000000000000000000000000000001100000000000000
#define AND         | 0b000000000000000000000000000000001101000000000000
#define OR          | 0b000000000000000000000000000000001110000000000000
#define XOR         | 0b000000000000000000000000000000001111000000000000
#define PCinc       & 0b111111111111111111111111111111111111011111111111
#define PCdec       & 0b111111111111111111111111111111111111101111111111
#define STACKinc    & 0b111111111111111111111111111111111111110111111111
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#define INTEREn     | 0b000000000000000000000000000000000000000000010000
#define INTERdis    | 0b000000000000000000000000000000000000000000001000
#define RESET       | 0b000000000000000000000000000000000000000000000100
#define HALT        | 0b000000000000000000000000000000000000000000000010
#define NextIns     & 0b111111111111111111111111111111111111111111111110

uint64_t MSK =       (uint64_t)0b000001110000000000000011111111110000111111100001;
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
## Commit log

2019-07-03 Add the Base Drawings
2019-07-05 Added Switching Register schematic and board
2019-07-07 added more boards
2019-07-12 Added the simple reg, cleaned things up
2019-07-12 Worked on the control board
2019-07-17 Add the control board
2019-07-17 Added the small flash boards
2019-07-19 Controller done?
2019-07-19 Added pdfs
2019-07-21 Added RAM
2019-07-27 Finish ALI Counter
2019-07-28 Finished All Boards
2019-07-28 fix the 16 register problem
2020-10-13 Fix problems with registers
2020-10-15 Check in the changes to the Controller
2020-11-08 Check in the first try at soldering up the board
2020-11-08 Add the 8bit compter
2020-11-16 Add the prototype stuff
2020-11-20 ALU Register and controllker layout
2020-12-06 add ram to Memory
